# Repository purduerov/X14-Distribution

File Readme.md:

# Readme for X14-Distribution

Whenever you make a new part, download the datasheet and save it here _**and**_ with the part in the parts library

Always pull other people's changes before beginning to work
`git pull`

Be sure to push your changes after  working on them. Run:
1. `git add .` to add any files in this directory or a subdirectory
or `git add -u` to add any modified files
2. (Optional) `git clean -nX` to see what ignored files can be removed
	`git clean -fX` removes ignored files (Eagle backups)
3. `git commit -m "helpful commit message"` with a description of the work that you did
4. `git push` to push your work to github

Other helpful commands
* `git status` says information about modified and staged files
* `git log` shows the recent commits of the repository
* `git log filename.extension` show the recent commits for just that file
* `git checkout first-couple-letter-of-commit-id` lets you go back to a previous version
* `git checkout master` brings you back to the latest commit
* `git tag` lists the tags
* `git tag -a orderX -m "the version of the board placed for the X'th order"` tag a specific commit
* `git push --tags` needed to push tags to remote
* `git show orderX` show the commit log for the given tag
* `git checkout orderX` go back and interact with the files at the tagged commit

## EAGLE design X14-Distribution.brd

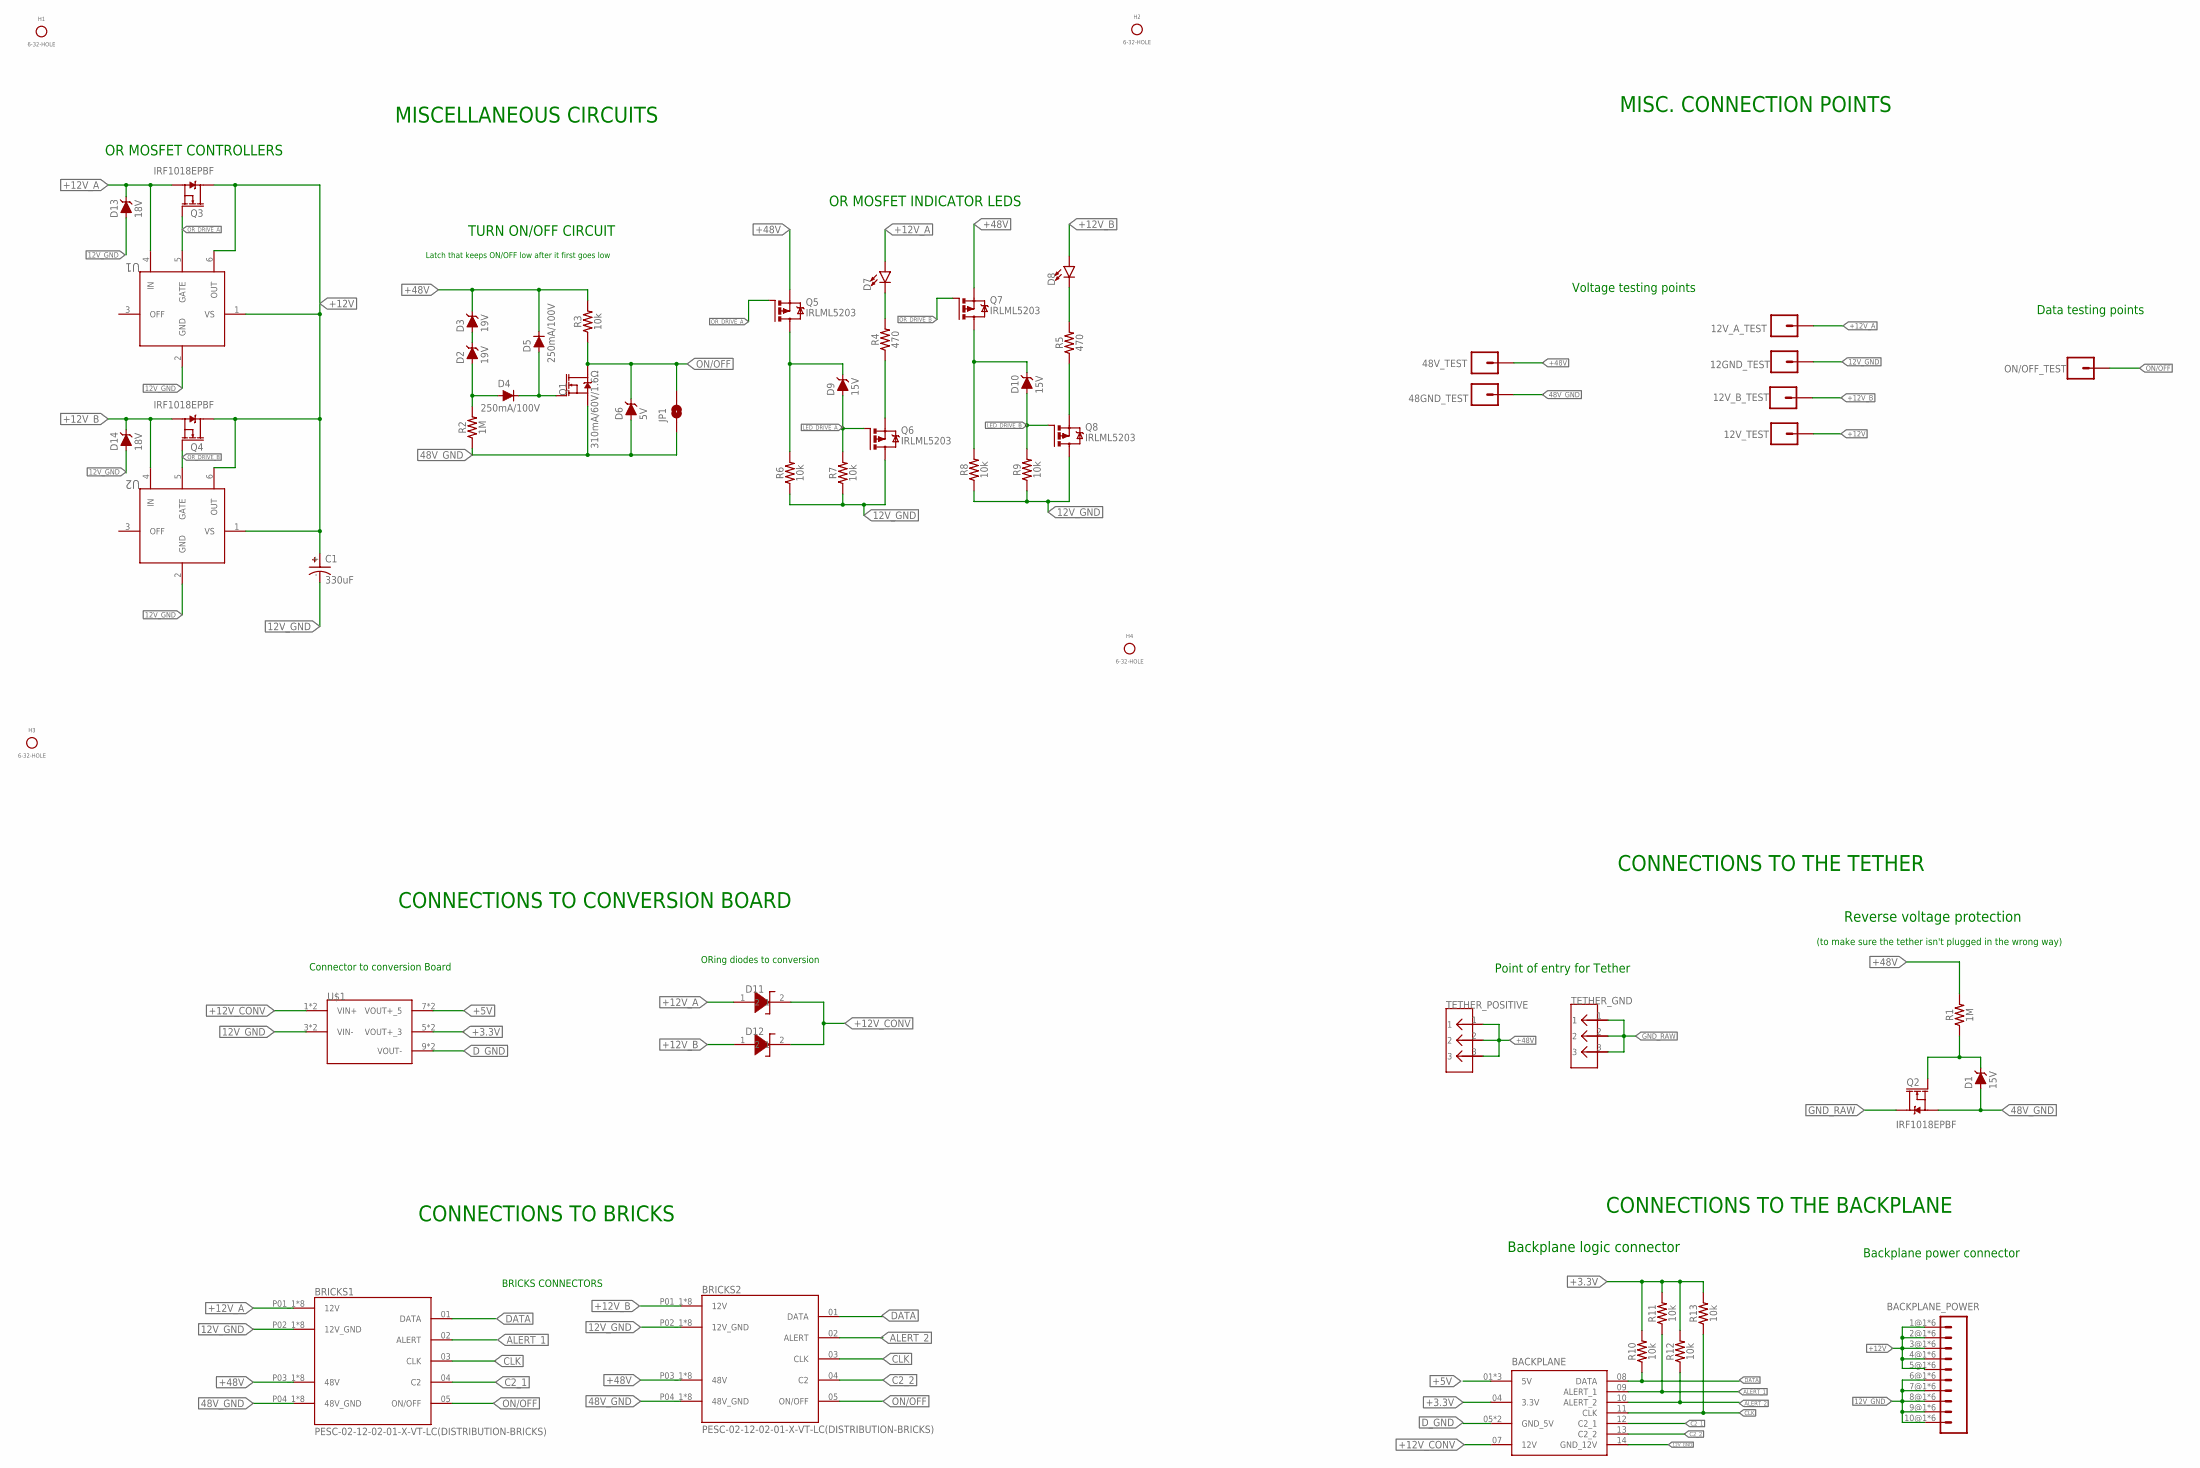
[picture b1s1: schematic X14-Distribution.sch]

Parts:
12GND_TEST, 12V_A_TEST, 12V_B_TEST, 12V_TEST, 48GND_TEST, 48V_TEST: CONN_01; 1X01
BACKPLANE: DISTRIBUTION-BACKPLANE; SAMTEC_IPL1-107-01-X-D-K(D-B)
BACKPLANE_POWER: MPPT-10-01-01-L-RA-SD
BRICKS1, BRICKS2: PESC-02-12-02-01-X-VT-LC(DISTRIBUTION-BRICKS); SAMTEC_PESC-02-12-02-01-X-VT-LC(D-B)
C1: 330uF; CAPAE1030X1050N
D1, D9, D10: 15V; SOD-323
D2, D3: 19V; SOD-323
D4, D5: 250mA/100V; SOD-323
D6: 5V; SOD-323
D7, D8: LED0603; LED-0603
D11, D12: DIODE-DO-214AC(SK34ATR)
D13, D14: 18V; PANASONIC_SMINI2-F5-B
H1, H2, H3, H4: 6-32-HOLE
JP1: JUMPER-SMT_2_NO_SILK; SMT-JUMPER_2_NO_SILK
ON/OFF_TEST: CONN_01; 1X01
Q1: 310mA/60V/1.6Ω; SOT323
Q2, Q3, Q4: IRF1018EPBF; TO263
Q5, Q6, Q7, Q8: IRLML5203; SOT23
R1, R2: 1M; 0603
R3, R6, R7, R8, R9, R10, R11, R12, R13: 10k; 0603
R4, R5: 470; 0603
TETHER_GND: 796636-3
TETHER_POSITIVE: 796636-3
U1, U2: DIST_OR_CONTROL_ALTMK06A-M; SOT-23-6
U$1: DISTRIBUTION-CONVERSION; TSW-105-05-G-S(D-C)

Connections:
12V_GND: 12GND_TEST.1, BACKPLANE.14 (GND_12V), BACKPLANE_POWER.6@1 (6), BACKPLANE_POWER.6@2 (6), BACKPLANE_POWER.6@3 (6), BACKPLANE_POWER.6@4 (6), BACKPLANE_POWER.6@5 (6), BACKPLANE_POWER.6@6 (6), BACKPLANE_POWER.7@1 (7), BACKPLANE_POWER.7@2 (7), BACKPLANE_POWER.7@3 (7), BACKPLANE_POWER.7@4 (7), BACKPLANE_POWER.7@5 (7), BACKPLANE_POWER.7@6 (7), BACKPLANE_POWER.8@1 (8), BACKPLANE_POWER.8@2 (8), BACKPLANE_POWER.8@3 (8), BACKPLANE_POWER.8@4 (8), BACKPLANE_POWER.8@5 (8), BACKPLANE_POWER.8@6 (8), BACKPLANE_POWER.9@1 (9), BACKPLANE_POWER.9@2 (9), BACKPLANE_POWER.9@3 (9), BACKPLANE_POWER.9@4 (9), BACKPLANE_POWER.9@5 (9), BACKPLANE_POWER.9@6 (9), BACKPLANE_POWER.10@1 (10), BACKPLANE_POWER.10@2 (10), BACKPLANE_POWER.10@3 (10), BACKPLANE_POWER.10@4 (10), BACKPLANE_POWER.10@5 (10), BACKPLANE_POWER.10@6 (10), BRICKS1.P02_1 (12V_GND), BRICKS1.P02_2 (12V_GND), BRICKS1.P02_3 (12V_GND), BRICKS1.P02_4 (12V_GND), BRICKS1.P02_5 (12V_GND), BRICKS1.P02_6 (12V_GND), BRICKS1.P02_7 (12V_GND), BRICKS1.P02_8 (12V_GND), BRICKS2.P02_1 (12V_GND), BRICKS2.P02_2 (12V_GND), BRICKS2.P02_3 (12V_GND), BRICKS2.P02_4 (12V_GND), BRICKS2.P02_5 (12V_GND), BRICKS2.P02_6 (12V_GND), BRICKS2.P02_7 (12V_GND), BRICKS2.P02_8 (12V_GND), C1.-, D13.A, D14.A, Q6.3 (D), Q8.3 (D), R6.1, R7.1, R8.1, R9.1, U1.2 (GND), U2.2 (GND), U$1.3 (VIN-), U$1.4 (VIN-)
48V_GND: 48GND_TEST.1, BRICKS1.P04_1 (48V_GND), BRICKS1.P04_2 (48V_GND), BRICKS1.P04_3 (48V_GND), BRICKS1.P04_4 (48V_GND), BRICKS1.P04_5 (48V_GND), BRICKS1.P04_6 (48V_GND), BRICKS1.P04_7 (48V_GND), BRICKS1.P04_8 (48V_GND), BRICKS2.P04_1 (48V_GND), BRICKS2.P04_2 (48V_GND), BRICKS2.P04_3 (48V_GND), BRICKS2.P04_4 (48V_GND), BRICKS2.P04_5 (48V_GND), BRICKS2.P04_6 (48V_GND), BRICKS2.P04_7 (48V_GND), BRICKS2.P04_8 (48V_GND), D1.A, D6.A, JP1.1, Q1.2 (S), Q2.2 (S), R2.1
+3.3V: BACKPLANE.04 (3.3V), R10.2, R11.2, R12.2, R13.2, U$1.5 (VOUT+_3), U$1.6 (VOUT+_3)
+5V: BACKPLANE.01 (5V), BACKPLANE.02 (5V), BACKPLANE.03 (5V), U$1.7 (VOUT+_5), U$1.8 (VOUT+_5)
+12V: 12V_TEST.1, BACKPLANE_POWER.1@1 (1), BACKPLANE_POWER.1@2 (1), BACKPLANE_POWER.1@3 (1), BACKPLANE_POWER.1@4 (1), BACKPLANE_POWER.1@5 (1), BACKPLANE_POWER.1@6 (1), BACKPLANE_POWER.2@1 (2), BACKPLANE_POWER.2@2 (2), BACKPLANE_POWER.2@3 (2), BACKPLANE_POWER.2@4 (2), BACKPLANE_POWER.2@5 (2), BACKPLANE_POWER.2@6 (2), BACKPLANE_POWER.3@1 (3), BACKPLANE_POWER.3@2 (3), BACKPLANE_POWER.3@3 (3), BACKPLANE_POWER.3@4 (3), BACKPLANE_POWER.3@5 (3), BACKPLANE_POWER.3@6 (3), BACKPLANE_POWER.4@1 (4), BACKPLANE_POWER.4@2 (4), BACKPLANE_POWER.4@3 (4), BACKPLANE_POWER.4@4 (4), BACKPLANE_POWER.4@5 (4), BACKPLANE_POWER.4@6 (4), BACKPLANE_POWER.5@1 (5), BACKPLANE_POWER.5@2 (5), BACKPLANE_POWER.5@3 (5), BACKPLANE_POWER.5@4 (5), BACKPLANE_POWER.5@5 (5), BACKPLANE_POWER.5@6 (5), C1.+, Q3.3 (D), Q4.3 (D), U1.1 (VS), U1.6 (OUT), U2.1 (VS), U2.6 (OUT)
+12V_A: 12V_A_TEST.1, BRICKS1.P01_1 (12V), BRICKS1.P01_2 (12V), BRICKS1.P01_3 (12V), BRICKS1.P01_4 (12V), BRICKS1.P01_5 (12V), BRICKS1.P01_6 (12V), BRICKS1.P01_7 (12V), BRICKS1.P01_8 (12V), D7.A, D11.1, D13.C, Q3.2 (S), U1.4 (IN)
+12V_B: 12V_B_TEST.1, BRICKS2.P01_1 (12V), BRICKS2.P01_2 (12V), BRICKS2.P01_3 (12V), BRICKS2.P01_4 (12V), BRICKS2.P01_5 (12V), BRICKS2.P01_6 (12V), BRICKS2.P01_7 (12V), BRICKS2.P01_8 (12V), D8.A, D12.1, D14.C, Q4.2 (S), U2.4 (IN)
+12V_CONV: BACKPLANE.07 (12V), D11.2, D12.2, U$1.1 (VIN+), U$1.2 (VIN+)
+48V: 48V_TEST.1, BRICKS1.P03_1 (48V), BRICKS1.P03_2 (48V), BRICKS1.P03_3 (48V), BRICKS1.P03_4 (48V), BRICKS1.P03_5 (48V), BRICKS1.P03_6 (48V), BRICKS1.P03_7 (48V), BRICKS1.P03_8 (48V), BRICKS2.P03_1 (48V), BRICKS2.P03_2 (48V), BRICKS2.P03_3 (48V), BRICKS2.P03_4 (48V), BRICKS2.P03_5 (48V), BRICKS2.P03_6 (48V), BRICKS2.P03_7 (48V), BRICKS2.P03_8 (48V), D3.C, D5.C, Q5.2 (S), Q7.2 (S), R1.2, R3.2, TETHER_POSITIVE.1, TETHER_POSITIVE.2, TETHER_POSITIVE.3
ALERT_1: BACKPLANE.09 (ALERT_1), BRICKS1.02 (ALERT), R11.1
ALERT_2: BACKPLANE.10 (ALERT_2), BRICKS2.02 (ALERT), R12.1
C2_1: BACKPLANE.12 (C2_1), BRICKS1.04 (C2)
C2_2: BACKPLANE.13 (C2_2), BRICKS2.04 (C2)
CLK: BACKPLANE.11 (CLK), BRICKS1.03 (CLK), BRICKS2.03 (CLK), R13.1
DATA: BACKPLANE.08 (DATA), BRICKS1.01 (DATA), BRICKS2.01 (DATA), R10.1
D_GND: BACKPLANE.05 (GND_5V), BACKPLANE.06 (GND_5V), U$1.9 (VOUT-), U$1.10 (VOUT-)
GND_RAW: Q2.3 (D), TETHER_GND.1, TETHER_GND.2, TETHER_GND.3
LED_DRIVE_A: D9.A, Q6.1 (G), R7.2
LED_DRIVE_B: D10.A, Q8.1 (G), R9.2
unnamed: D1.C, Q2.1 (G), R1.1
unnamed: D4.C, D5.A, Q1.1 (G)
unnamed: Q6.2 (S), R4.1
unnamed: D2.C, D3.A
unnamed: D9.C, Q5.3 (D), R6.2
unnamed: D2.A, D4.A, R2.2
unnamed: Q8.2 (S), R5.1
unnamed: D10.C, Q7.3 (D), R8.2
unnamed: D7.C, R4.2
unnamed: D8.C, R5.2
ON/OFF: BRICKS1.05 (ON/OFF), BRICKS2.05 (ON/OFF), D6.C, JP1.2, ON/OFF_TEST.1, Q1.3 (D), R3.1
OR_DRIVE_A: Q3.1 (G), Q5.1 (G), U1.5 (GATE)
OR_DRIVE_B: Q4.1 (G), Q7.1 (G), U2.5 (GATE)

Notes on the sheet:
OR MOSFET INDICATOR LEDS
Backplane logic connector
OR MOSFET CONTROLLERS
ORing diodes to conversion
Reverse voltage protection
TURN ON/OFF CIRCUIT
Latch that keeps ON/OFF low after it first goes low
BRICKS CONNECTORS
Connector to conversion Board
Voltage testing points
CONNECTIONS TO CONVERSION BOARD
CONNECTIONS TO BRICKS
MISC. CONNECTION POINTS
CONNECTIONS TO THE TETHER
Backplane power connector
Data testing points
Point of entry for Tether
CONNECTIONS TO THE BACKPLANE
(to make sure the tether isn't plugged in the wrong way)
MISCELLANEOUS CIRCUITS

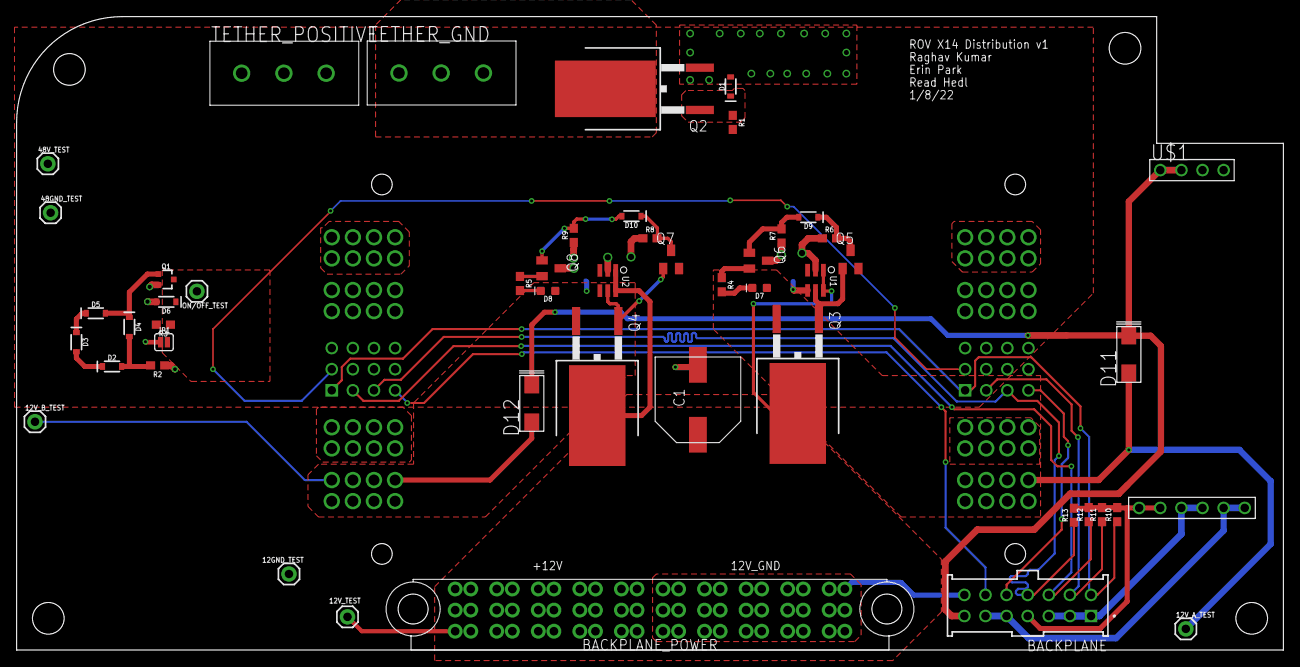
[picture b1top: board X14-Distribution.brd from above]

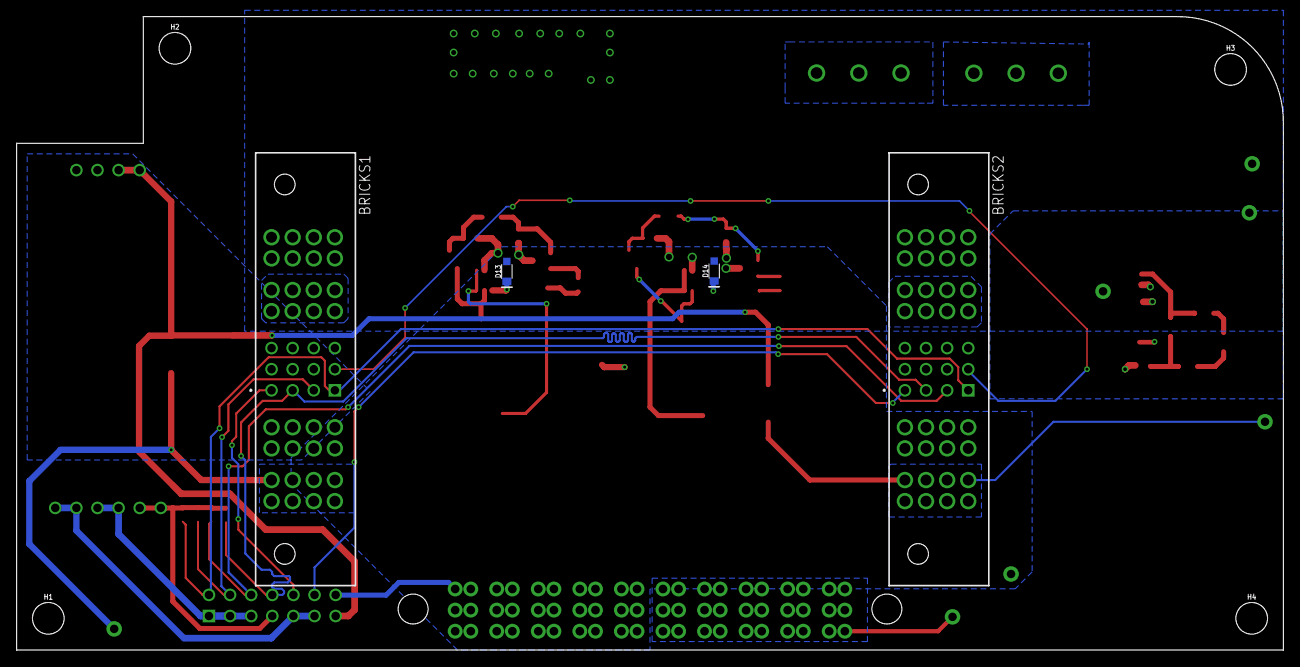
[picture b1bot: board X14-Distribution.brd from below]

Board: 2 copper layers, 152.4 x 76.2 mm, 57 parts (8 on the bottom side), 32 nets.

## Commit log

2021-09-18 readme+gitignore
2021-09-25 added schematic file with only frame to the repository
2021-10-02 Added the Reverse voltage blocker from the tether, OR MOSFET controller, and ON/OFF signal for Bricks
2021-10-04 Added the schottky diode ORing for the conversion board
2021-10-05 Added the test points, points of entry for different voltage levels, and power connection to the Backplane
2021-10-13 Added conversion board connector
2021-10-16 Added descriptive green text and some connectors
2021-10-20 Added connectors to Bricks and some more extra green explanation text
2021-10-21 Added more green explanatory text, and spread out the schematic to make it look better
2021-10-21 Made a little spacing change
2021-10-28 Changed footprint of schottky diode
2021-10-30 Changed ORing LED MOSFETs to p-channel TSM2309CX RFG
2021-10-30 Changed the p-mosfets to be oriented the right way
2021-10-30 Fixed some junction connection errors
2021-11-03 Changed the Backplane Logic connector
2021-11-03 Added board file
2021-11-10 added board dimensions
2021-11-20 Made some changes for the board
2021-11-24 Made some changes to board and added 18V zener diodes from 12V_A and B to ground
2021-11-29 didn't change anything
2021-12-01 Made some more changes to the board
2021-12-01 Made changes to the board
2021-12-01 made more board changes
2021-12-02 Changed a lot of stuff on the board
2021-12-02 More board stuff
2021-12-02 Made more changes to the board
2021-12-04 Moved the ON/OFF circuit
2021-12-04 made some more changes
2021-12-04 Corrected a wire on the board
2021-12-04 Chagned some wires to make it fit DRC
2021-12-04 Mad e more changes
2021-12-04 Maybe done?
2021-12-08 moved on/off circuit
2021-12-11 Length-matched the DATA and CLK lines
2021-12-11 Made a few more changes to the same board
2021-12-11 Finished all design review changes, except bricks connector
2021-12-11 Made changes according to Grant's notes
2021-12-11 Changed curves back to zigzagy thingys
2021-12-21 All changes except for bricks outlines
2021-12-25 Made some changes
2021-12-30 Added Bricks outline
2021-12-30 added brick outline. Fixed a git error
2022-01-01 Added the brick outline footprint
2022-01-01 Fixed the DRC errors
2022-01-02 Changed the reverse voltage circuit to be horizontal
2022-01-02 Small change
2022-01-02 Some more changes
2022-01-07 added silkscreen, moved testpoints
2022-01-26 STEPS!
2022-03-14 Updated Step

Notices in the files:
parts and their libraries:
SparkFun-Connectors: Licensing: Creative Commons ShareAlike 4.0 International - https://creativecommons.org/licenses/by-sa/4.0
